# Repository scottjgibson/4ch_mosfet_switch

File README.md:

4ch_mosfet_switch
=================

4ch logic driven mosfet switch

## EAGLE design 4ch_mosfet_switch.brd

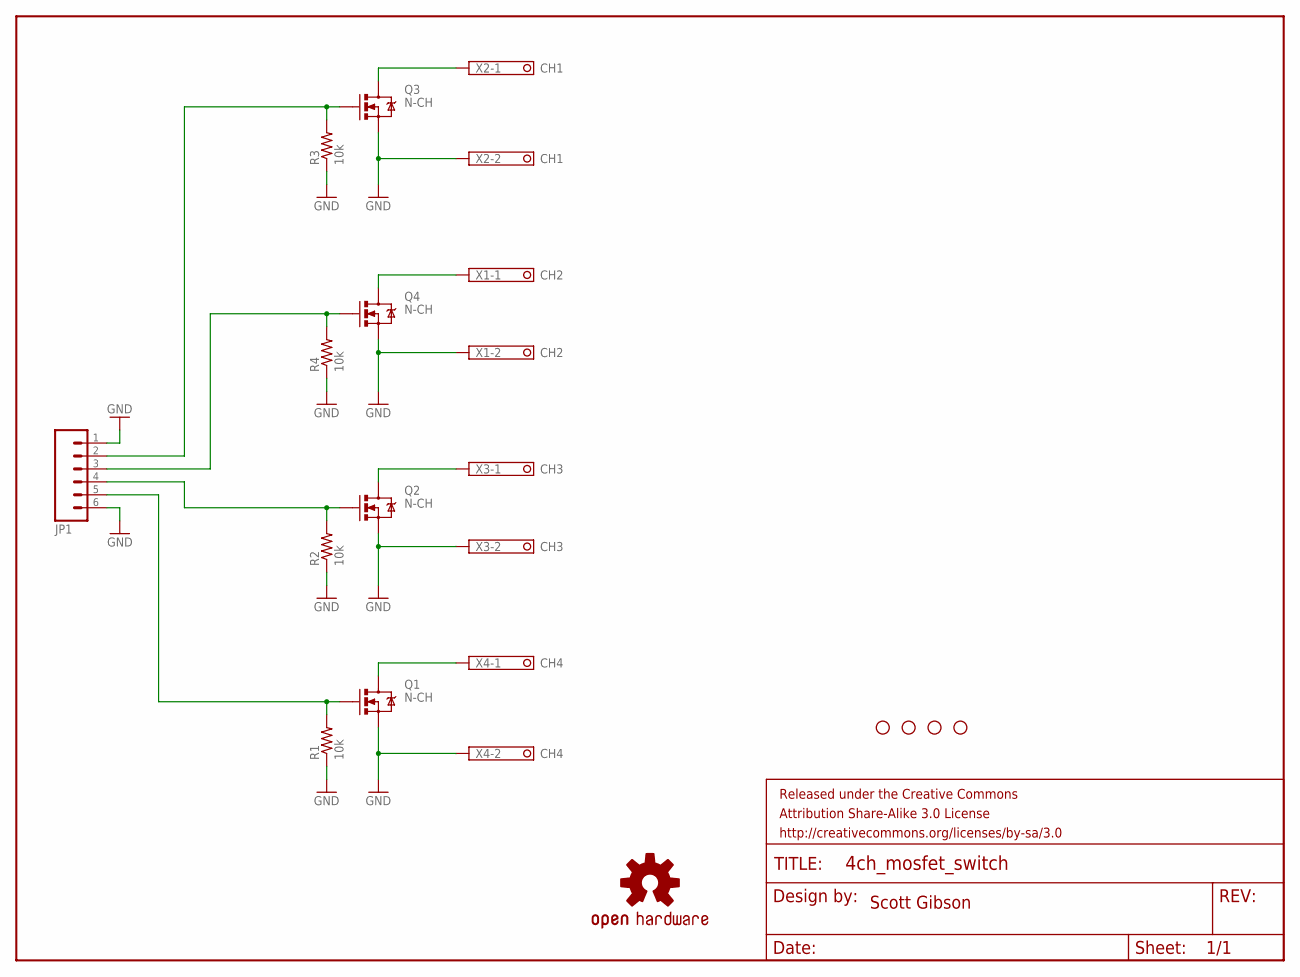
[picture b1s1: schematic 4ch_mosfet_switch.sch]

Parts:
FRAME1: FRAME-LETTER; CREATIVE_COMMONS
JP1: M06LOCK_LONGPADS; 1X06_LOCK_LONGPADS
LOGO1: OSHW-LOGOM; OSHW-LOGO-M
Q1, Q2, Q3, Q4: N-CH; TO220V
R1, R2, R3, R4: 10k; AXIAL-0.3
STANDOFF1, STANDOFF2, STANDOFF3, STANDOFF4: STAND-OFF
X1: CH2; 1751248
X2: CH1; 1751248
X3: CH3; 1751248
X4: CH4; 1751248

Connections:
GND: JP1.1, JP1.6, Q1.3 (S), Q2.3 (S), Q3.3 (S), Q4.3 (S), R1.P$1 (1), R2.P$1 (1), R3.P$1 (1), R4.P$1 (1), X1.2, X2.2, X3.2, X4.2
unnamed: JP1.3, Q4.1 (G), R4.P$2 (2)
unnamed: JP1.2, Q3.1 (G), R3.P$2 (2)
unnamed: JP1.4, Q2.1 (G), R2.P$2 (2)
unnamed: JP1.5, Q1.1 (G), R1.P$2 (2)
unnamed: Q1.2 (D), X4.1
unnamed: Q2.2 (D), X3.1
unnamed: Q3.2 (D), X2.1
unnamed: Q4.2 (D), X1.1

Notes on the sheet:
Scott Gibson

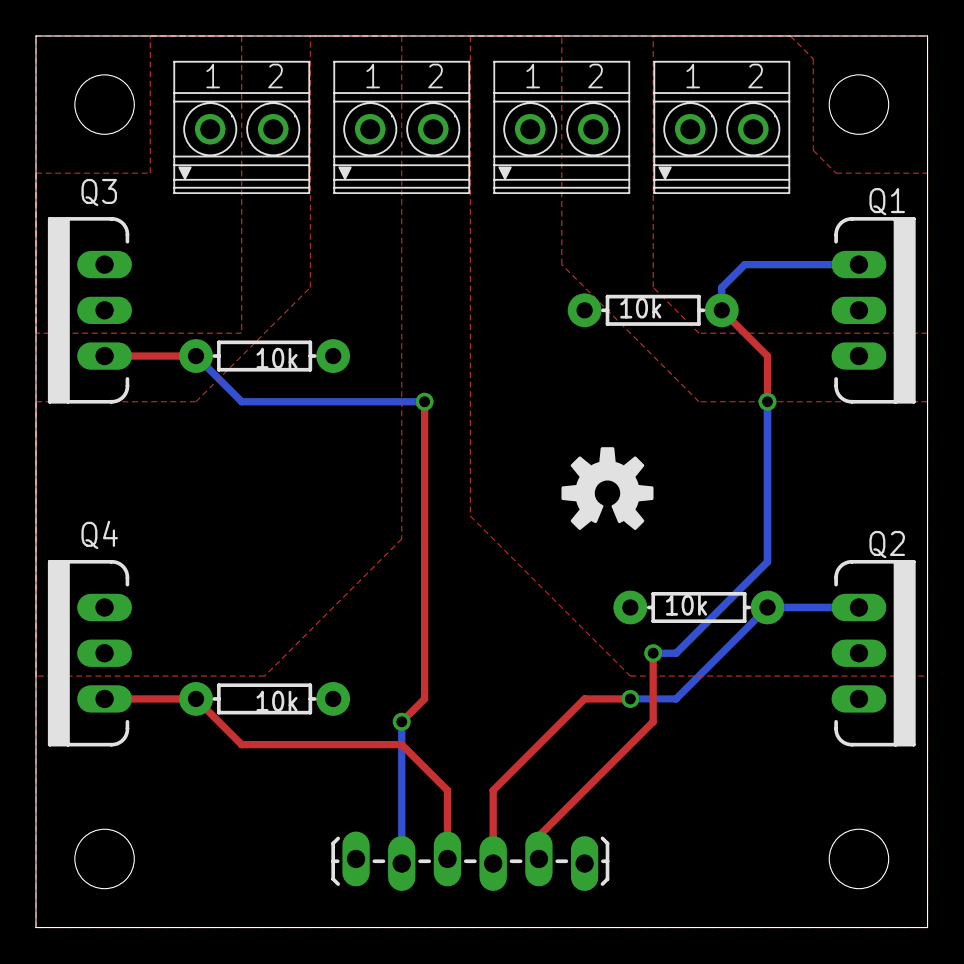
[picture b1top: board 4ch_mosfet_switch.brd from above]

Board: 2 copper layers, 49.5 x 49.5 mm, 19 parts (0 on the bottom side), 9 nets.

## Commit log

2013-08-28 Adding PDF Schematic and Layout
2013-09-06 Updated Names

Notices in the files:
parts and their libraries:
SparkFun-Aesthetics: Licensing: CC v3.0 Share-Alike You are welcome to use this library for commercial purposes.
SparkFun-Aesthetics: Released under the Creative Commons Attribution Share-Alike 3.0 License
SparkFun-Aesthetics: http://creativecommons.org/licenses/by-sa/3.0
